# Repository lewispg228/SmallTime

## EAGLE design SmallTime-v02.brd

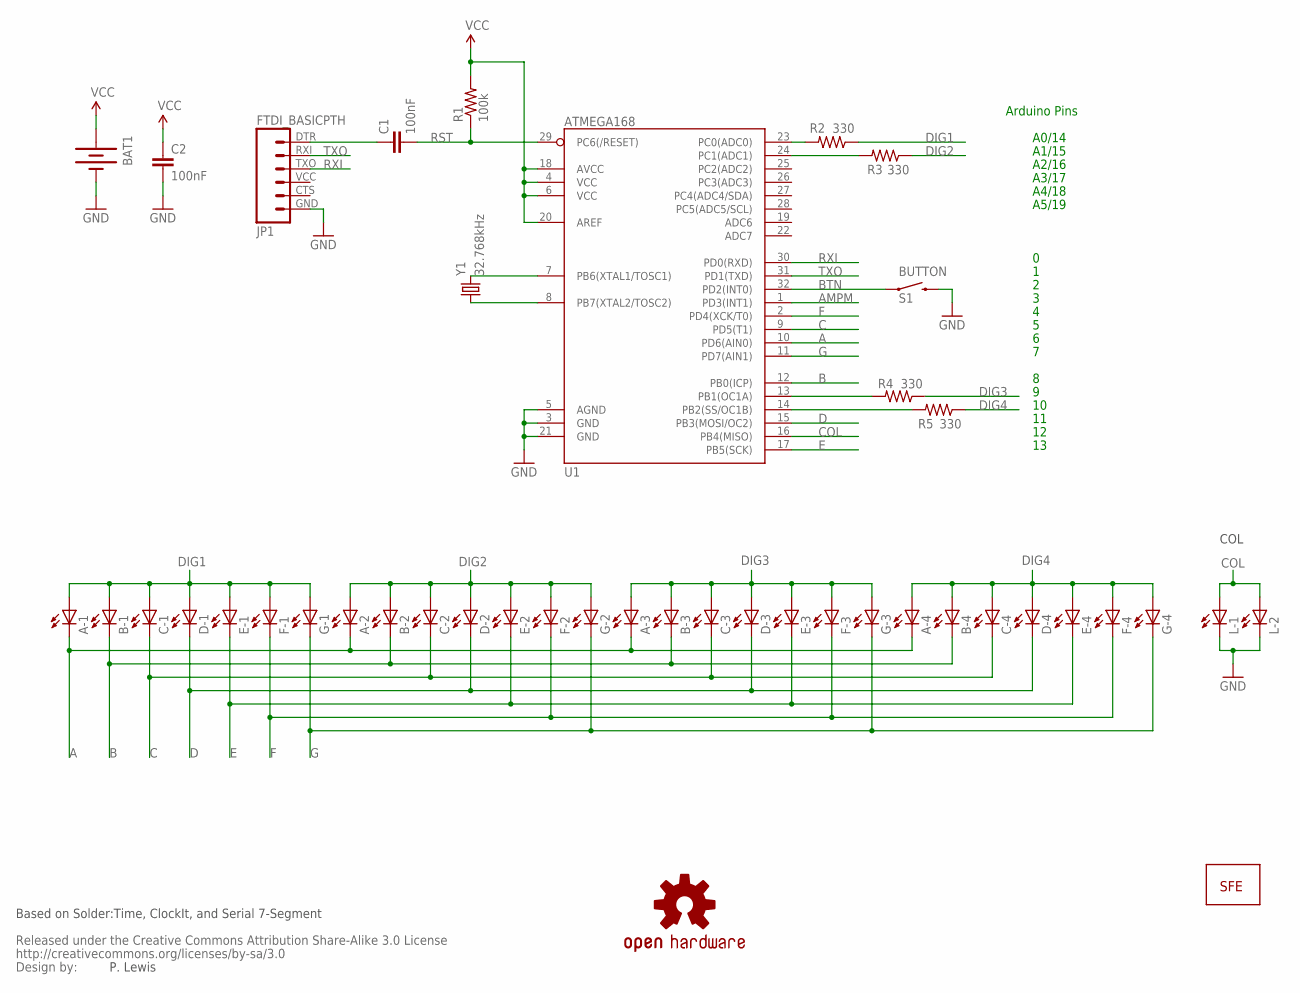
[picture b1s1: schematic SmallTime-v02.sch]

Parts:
A-1, A-2, A-3, A-4: LEDBOTTOM; LED-1206-BOTTOM-TINGHT
B-1, B-2, B-3, B-4: LEDBOTTOM; LED-1206-BOTTOM-TINGHT
BAT1: BATTERYFOB; BATTERY_20MM_PTH_COMPACT
C1, C2: 100nF; 0603-CAP
C-1, C-2, C-3, C-4: LEDBOTTOM; LED-1206-BOTTOM-TINGHT
D-1, D-2, D-3, D-4: LEDBOTTOM; LED-1206-BOTTOM-TINGHT
E-1, E-2, E-3, E-4: LEDBOTTOM; LED-1206-BOTTOM-TINGHT
F-1, F-2, F-3, F-4: LEDBOTTOM; LED-1206-BOTTOM-TINGHT
G-1, G-2, G-3, G-4: LEDBOTTOM; LED-1206-BOTTOM-TINGHT
JP1: FTDI_BASICPTH; FTDI_BASIC
L-1, L-2: LEDBOTTOM; LED-1206-BOTTOM-TINGHT
R1: 100k; 0603-RES
R2, R3, R4, R5: 330; 0603-RES
S1: BUTTON; TACTILE-PTH-SIDEEZ
U1: ATMEGA168; TQFP32-08
U$2: CREATIVE_COMMONS
U$4: OSHW-LOGOS; OSHW-LOGO-S
U$5: LOGO-SFENW2; SFE-NEW-WEB
Y1: 32.768kHz; TC26HEZ

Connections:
A: A-1.C, A-2.C, A-3.C, A-4.C, U1.10 (PD6(AIN0))
AMPM: U1.1 (PD3(INT1))
B: B-1.C, B-2.C, B-3.C, B-4.C, U1.12 (PB0(ICP))
BTN: S1.1, U1.32 (PD2(INT0))
C: C-1.C, C-2.C, C-3.C, C-4.C, U1.9 (PD5(T1))
COL: L-1.A, L-2.A, U1.16 (PB4(MISO))
D: D-1.C, D-2.C, D-3.C, D-4.C, U1.15 (PB3(MOSI/OC2))
DIG1: A-1.A, B-1.A, C-1.A, D-1.A, E-1.A, F-1.A, G-1.A, R2.1
DIG2: A-2.A, B-2.A, C-2.A, D-2.A, E-2.A, F-2.A, G-2.A, R3.1
DIG3: A-3.A, B-3.A, C-3.A, D-3.A, E-3.A, F-3.A, G-3.A, R4.1
DIG4: A-4.A, B-4.A, C-4.A, D-4.A, E-4.A, F-4.A, G-4.A, R5.1
E: E-1.C, E-2.C, E-3.C, E-4.C, U1.17 (PB5(SCK))
F: F-1.C, F-2.C, F-3.C, F-4.C, U1.2 (PD4(XCK/T0))
G: G-1.C, G-2.C, G-3.C, G-4.C, U1.11 (PD7(AIN1))
GND: BAT1.2 (-), C2.2, JP1.GND (6), L-1.C, L-2.C, S1.2, U1.3 (GND), U1.5 (AGND), U1.21 (GND)
unnamed: U1.8 (PB7(XTAL2/TOSC2)), Y1.1
unnamed: U1.7 (PB6(XTAL1/TOSC1)), Y1.2
unnamed: C1.1, JP1.DTR (1)
unnamed: R4.2, U1.13 (PB1(OC1A))
unnamed: R5.2, U1.14 (PB2(SS/OC1B))
unnamed: R3.2, U1.24 (PC1(ADC1))
unnamed: R2.2, U1.23 (PC0(ADC0))
RST: C1.2, R1.1, U1.29 (PC6(/RESET))
RXI: JP1.TXO (3), U1.30 (PD0(RXD))
TXO: JP1.RXI (2), U1.31 (PD1(TXD))
VCC: BAT1.1 (+), C2.1, R1.2, U1.4 (VCC), U1.6 (VCC), U1.18 (AVCC), U1.20 (AREF)

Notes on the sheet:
P. Lewis
A0/14
A1/15
A2/16
A3/17
A4/18
A5/19
Arduino Pins
Based on Solder:Time, ClockIt, and Serial 7-Segment
COL

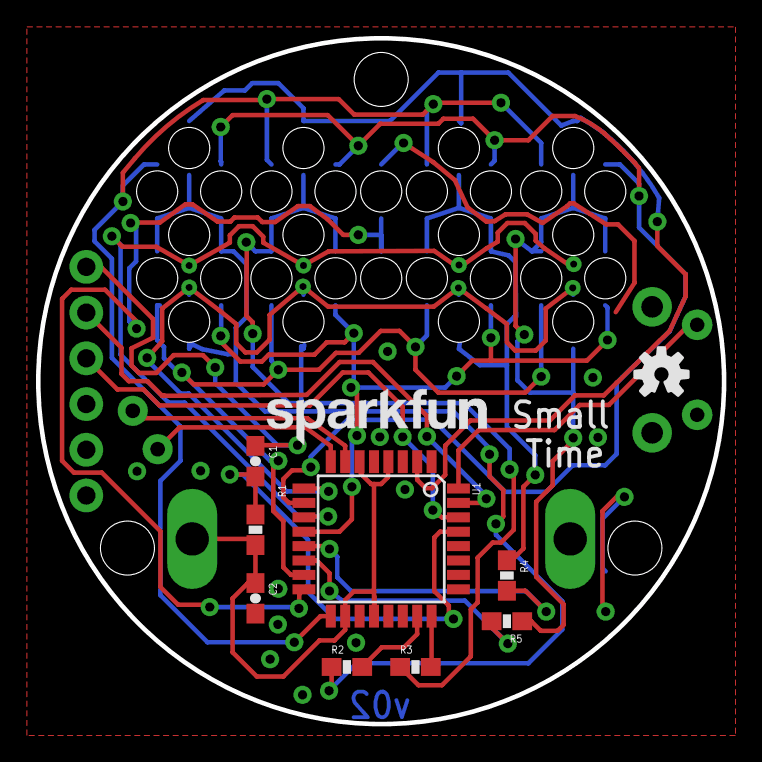
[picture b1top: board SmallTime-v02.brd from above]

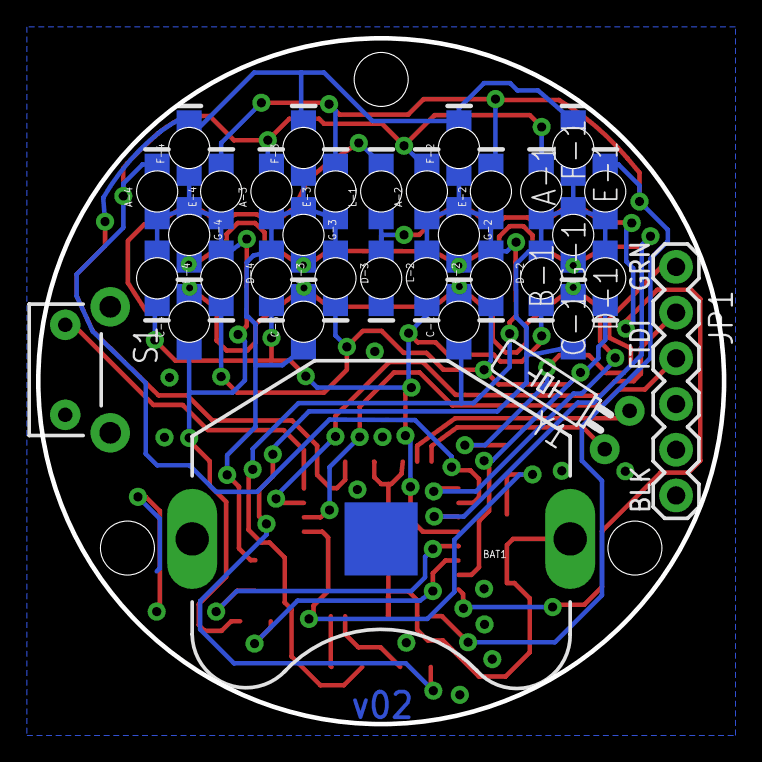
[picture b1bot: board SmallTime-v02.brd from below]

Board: 2 copper layers, 38.1 x 38.1 mm, 45 parts (34 on the bottom side), 25 nets.

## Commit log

2013-01-15 Improved design
    Spaced segment LEDs more evenly, moved resistors to make more clearing
    for enclosure peices, cleaned up routing.

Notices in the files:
parts and their libraries:
SparkFun: Released under the Creative Commons Attribution Share-Alike 3.0 License
SparkFun: http://creativecommons.org/licenses/by-sa/3.0
SparkFun-Passives: Licensing: CC v3.0 Share-Alike You are welcome to use this library for commercial purposes.
